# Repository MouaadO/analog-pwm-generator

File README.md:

# Analog PWM Generator with Adjustable Dead Time

**20–100 kHz · Complementary 5 V outputs · Stackable control PCB**

An analog PWM generator with adjustable frequency, duty cycle and dead time. The circuit uses a shared triangular carrier, comparison thresholds and output buffers. Its stackable PCB supplies the switching commands for the [58 W synchronous buck converter](https://github.com/MouaadO/synchronous-buck-converter), the second project in the electric-scooter auxiliary-power system.

**Project team:** Amani Mouaad and Cheiffou Melissa.  
**IFP SCHOOL · Powertrain · 2026/2027**

## The control half of a two-board system

The PWM board handles the low-level timing commands. The buck power board receives those commands through the Uno Rev3-compatible headers and drives its two power MOSFETs. Keeping the boards separate makes the timing circuit easy to adjust and the power stage easy to inspect.

| Function | Design target |
|---|---|
| Outputs | Two complementary PWM signals |
| Switching frequency | 20–100 kHz |
| Duty command | 0–100%, selected from a potentiometer or external SMA input |
| Dead-time adjustment | Up to 10% of the switching period |
| Logic levels | Nominal 0 V / 5 V |
| Drive current | More than 20 mA source and sink per output |
| Supply | 7–10 V DC, centre-positive barrel jack |

## How the signal becomes PWM

1. **Carrier generation:** An integrator produces a rising/falling triangular voltage. A comparator with hysteresis reverses the clock at the carrier limits.
2. **Command selection:** The selector chooses the duty potentiometer or the external SMA command.
3. **Threshold generation:** A resistor network combines the command with the dead-time setting to establish two comparison levels.
4. **Comparison:** The triangle crosses those levels at different instants, creating the two complementary pulse allocations and their non-overlap intervals.
5. **Output drive:** The buffer stages drive OUT1 and OUT2. Endpoint detectors establish constant states for external commands outside the operating interval.

## Oscillator and timing equations

For timing resistance $R_t$ and integrator capacitor $C_{INT}$:

$$I=\frac{CLOCK-V_m}{R_t},\qquad
\frac{dV_{TRI}}{dt}=-\frac{I}{C_{INT}}$$

The comparator limits and the integrator slope determine the period. For the chosen resistor ratio, the nominal frequency relation is:

$$f\simeq\frac{3}{R_tC_{INT}}$$

The shared carrier keeps the frequency, command and dead-time comparison tied to one switching period. Detailed threshold and frequency calculations are in the [design notes](docs/design-notes.md).

## Current stackable PCB

The current board is **75 × 53 mm**, with a 7 mm extension on the potentiometer side. The extension places the outward-facing controls, regulator and input connectors in the exposed area of the two-board assembly. The 32 mating contacts retain the official Uno Rev3 pattern.

### Top 3D view

### Header connections to the buck board

| Signal | PWM-board pad | Uno contact |
|---|---|---|
| OUT1 / PWM1 | J4 pin 9 | D9 |
| OUT2 / PWM2 | J4 pin 8 | D10 |
| Common ground | J4 pin 4; J6 pins 6–7 | GND |

The upper board is the [synchronous buck converter](https://github.com/MouaadO/synchronous-buck-converter). Its battery input and 12 V gate-driver supply use separate power terminals.

### Front and back layers

| Front copper | Back copper |
|---|---|
|  |  |

Signal tracks use 0.25 mm widths, PWM output routes 0.40 mm, and supply/ground routes 0.50 mm. The front copper fill distributes 5 V; the back fill provides ground. Local footprints and bundled models define the potentiometers, connectors and IC packages.

### Complete schematic

## Recorded LTspice results

The existing simulation uses the 7805 supply model. The PCB assembly uses the selected LF50ABV regulator. The following values are the recorded **LTspice results** for the supplied simulation settings:

| Quantity | Result |
|---|---:|
| Frequency endpoints | 19.99 kHz / 99.69 kHz |
| Output LOW / HIGH | 0.082 V / 4.916 V |
| Source/sink current | Approximately 26.86 mA per output |
| Fast-setting non-overlap gaps | 0.980 µs / 0.984 µs |

## Open and run

For the hardware, open [pcb/Analog_PWM.kicad_pro](pcb/Analog_PWM.kicad_pro) in KiCad 8 or newer. In PCB Editor, press **Alt+3** for the 3D viewer. Keep the local symbol library, footprint library, tables and `3dmodels` folder beside the project.

For simulation, open `simulation/analog_pwm_dead_time.asc` in LTspice and run its transient analysis. Probe `TRI`, `CMD`, `LOW`, `HIGH`, `OUT1` and `OUT2`. Parameters `FP`, `DP`, `DTP`, `SOURCE` and `VD` select the operating settings.

## Files and tools

| Location | Contents |
|---|---|
| `pcb/` | KiCad schematic, board, local libraries, assembly BOM and purchasing workbook |
| `pcb/Manufacturing/` | Gerbers and plated/non-plated drill outputs |
| `simulation/` | LTspice schematic, symbols and component libraries |
| [Design notes](docs/design-notes.md) | Oscillator, duty and threshold calculations |
| `docs/images/` | PCB, schematic and stacked-system renders |
| `docs/datasheets/` | Component datasheets |

**Tools:** LTspice, KiCad, manufacturer package drawings and local 3D models.

## Related projects

[58 W Synchronous Buck Converter](https://github.com/MouaadO/synchronous-buck-converter) · [Inverter Modulation and PWM](https://github.com/MouaadO/inverter-pwm-experimental-validation)

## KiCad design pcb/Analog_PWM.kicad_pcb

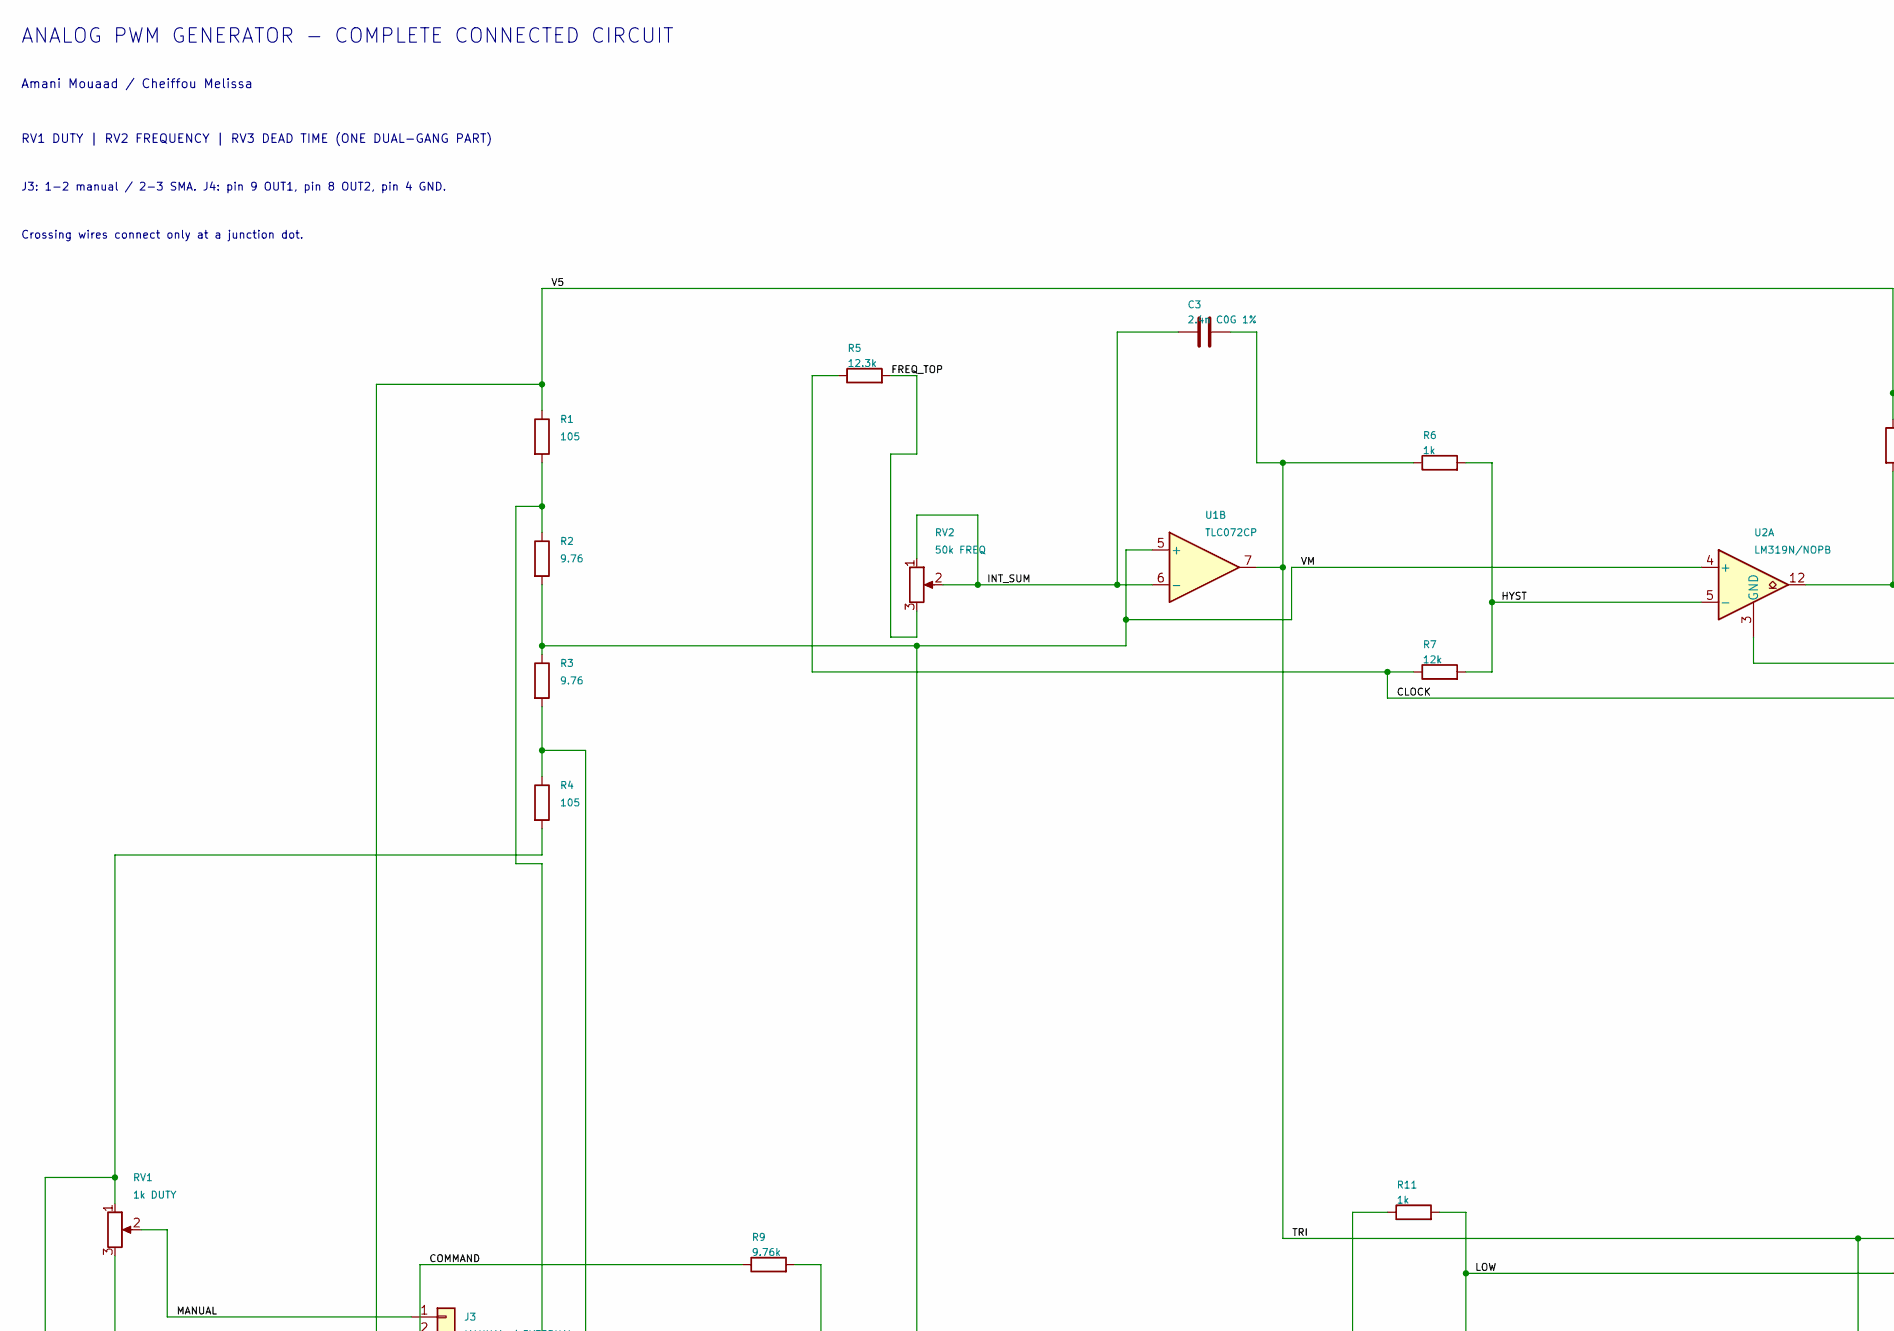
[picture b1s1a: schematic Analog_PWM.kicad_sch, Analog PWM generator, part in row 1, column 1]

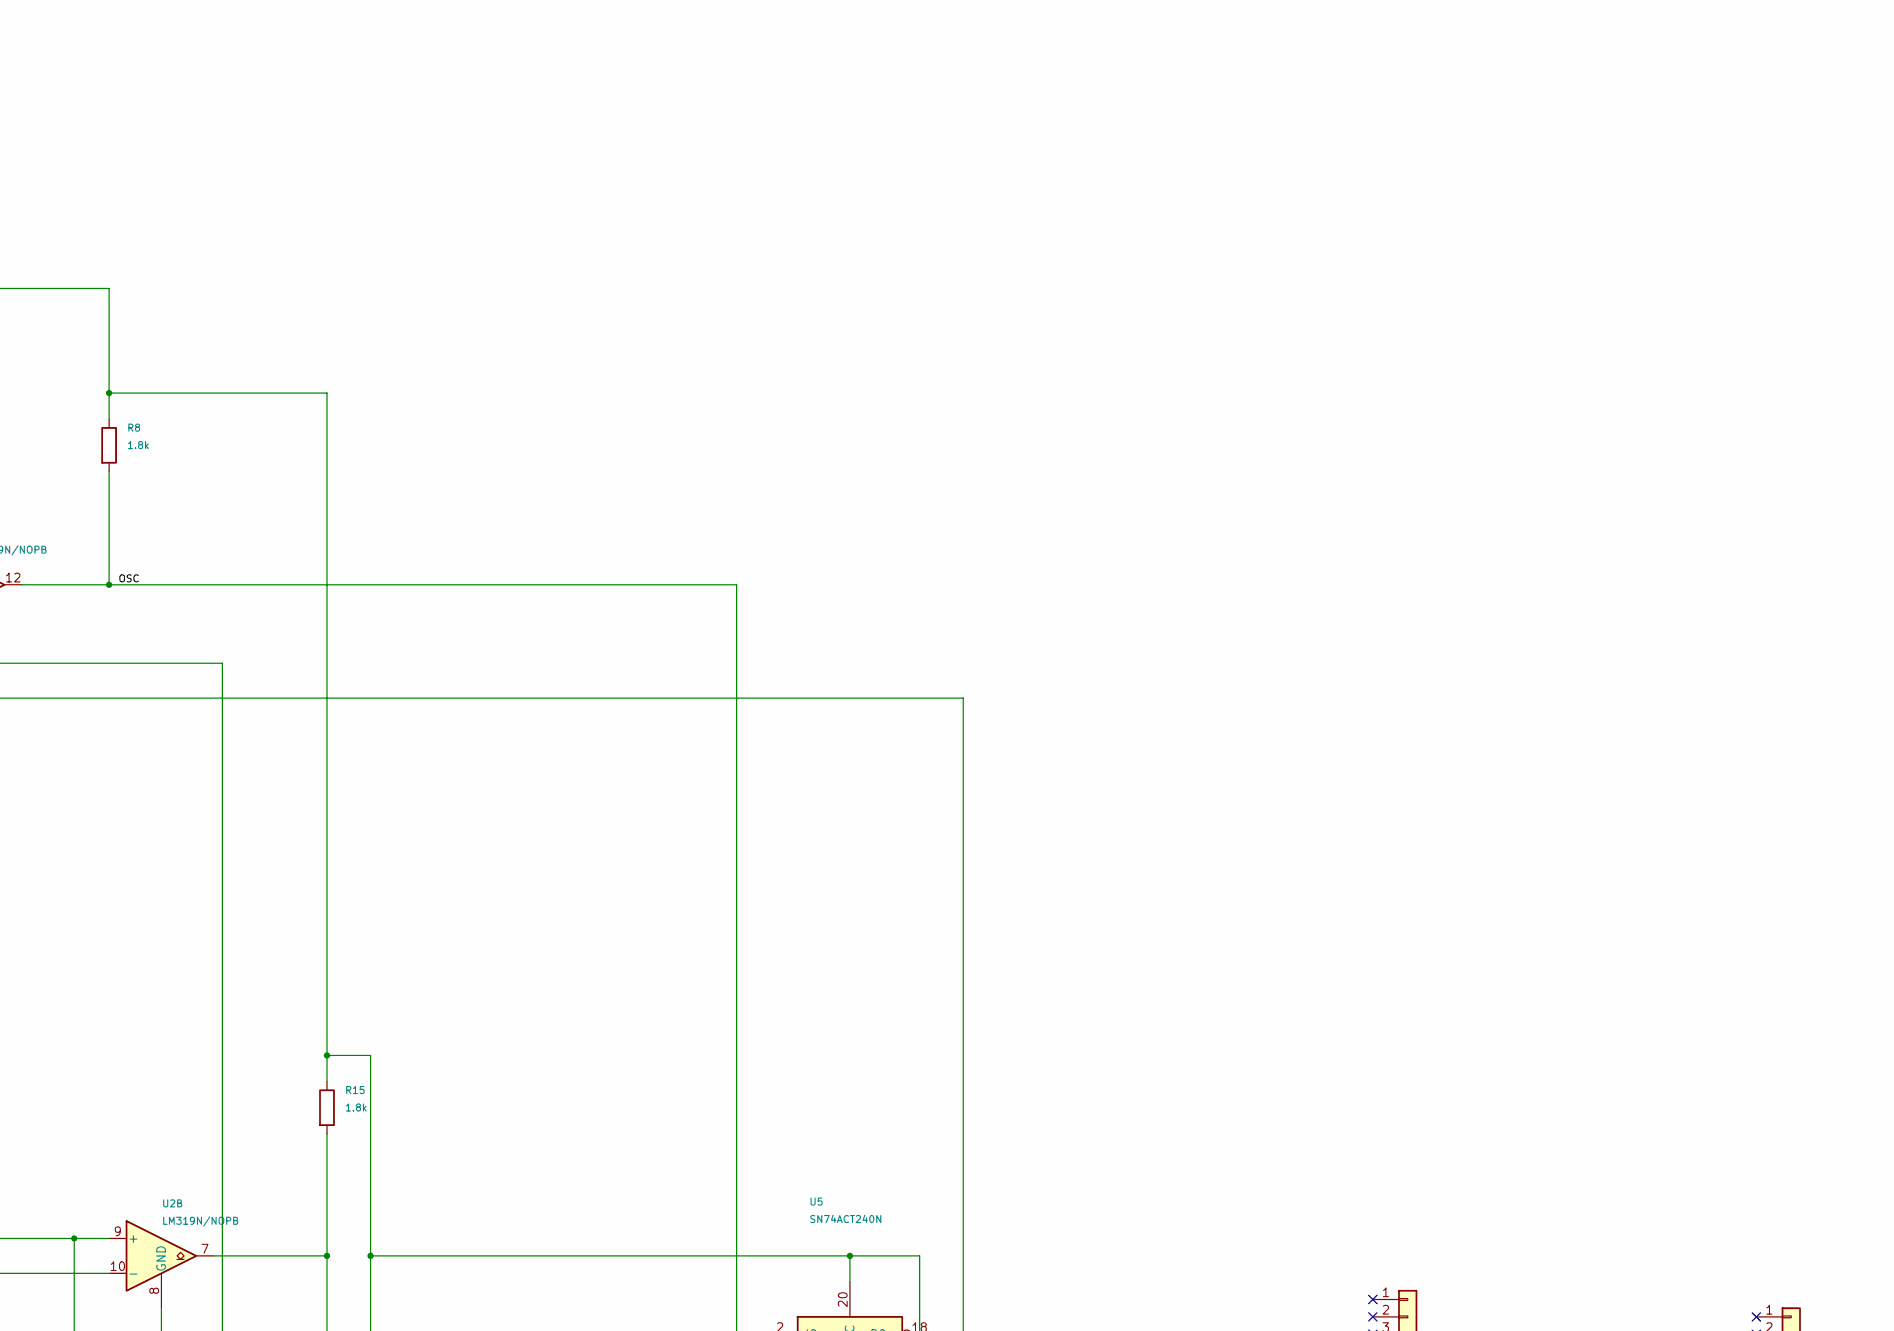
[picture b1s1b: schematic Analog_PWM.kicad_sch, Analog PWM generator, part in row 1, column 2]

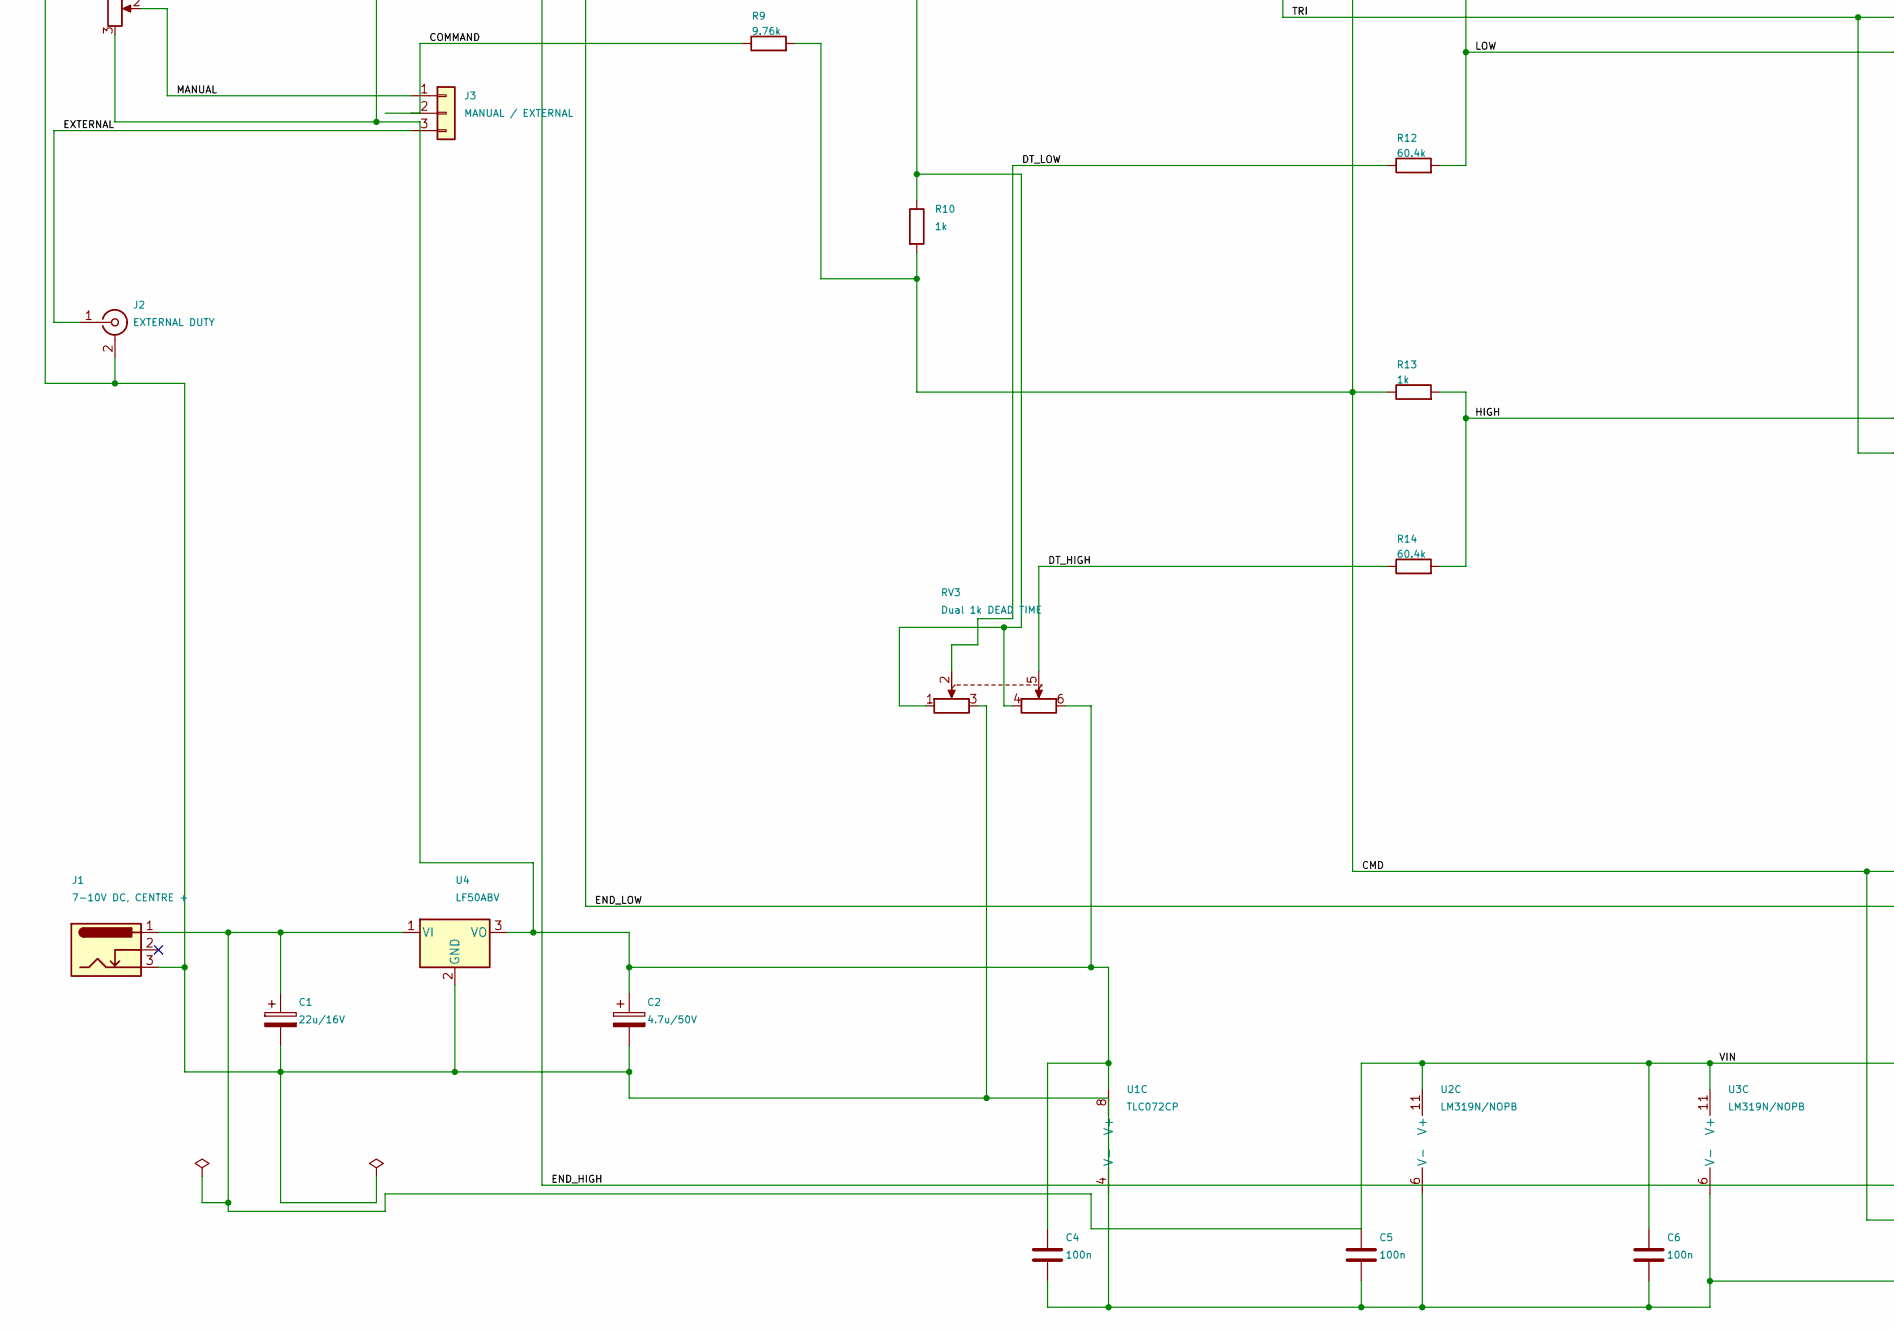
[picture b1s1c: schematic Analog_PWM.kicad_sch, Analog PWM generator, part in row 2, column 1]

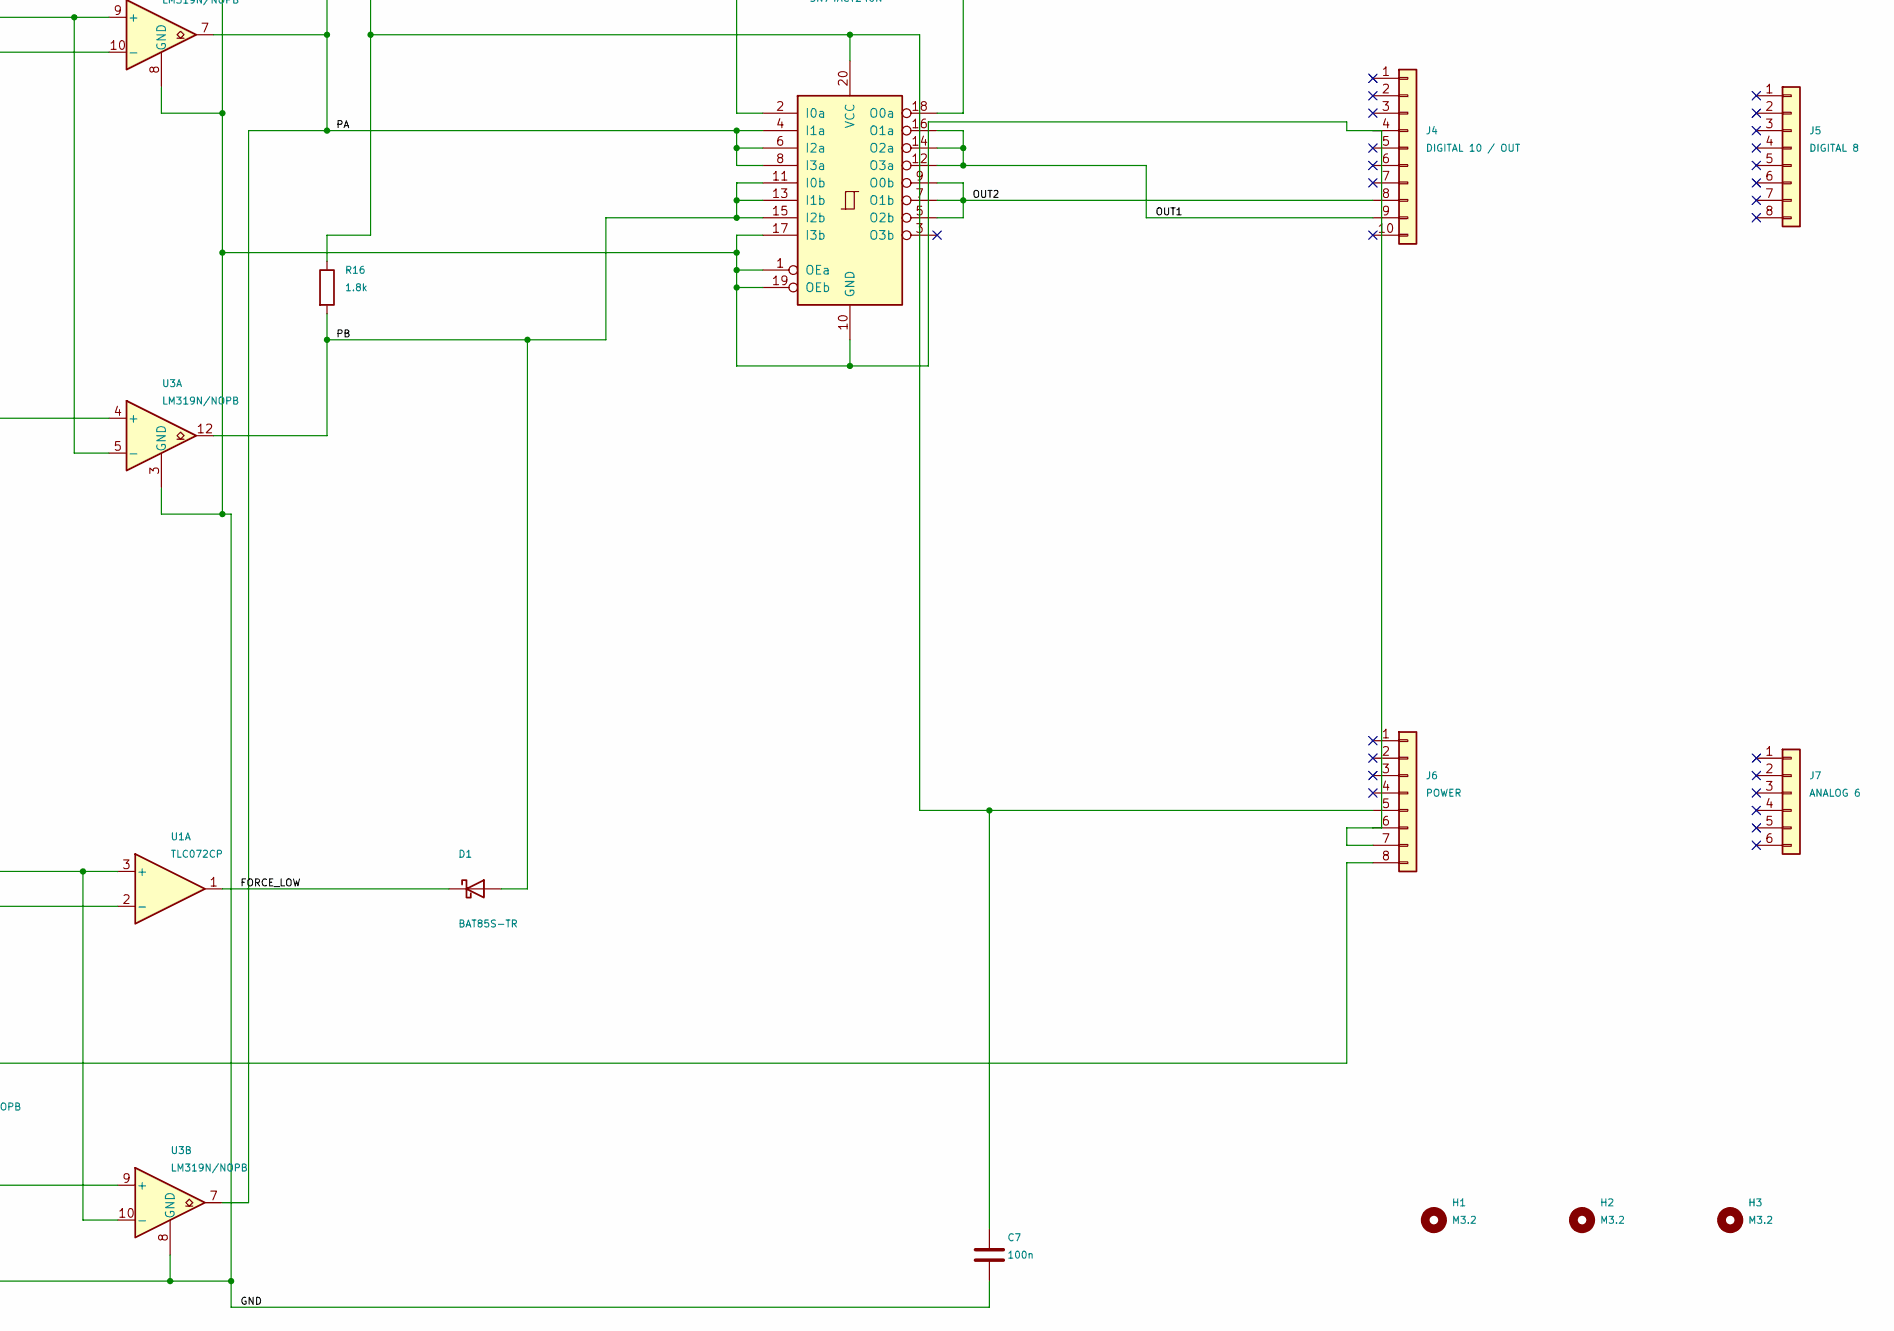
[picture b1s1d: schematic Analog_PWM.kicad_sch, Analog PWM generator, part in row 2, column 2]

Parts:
C1: 22u/16V; CP_Radial_D5.0mm_P2.00mm; MPN MCGPR16V226M5X11
C2: 4.7u/50V; CP_Radial_D5.0mm_P2.50mm; MPN EEU-FC1H4R7H
C3: 2.4n C0G 1%; C317_5.08mm; MPN C317C242F3G5TA
C4, C5, C6, C7: 100n; Vishay_K15_P2.5mm; MPN K104K15X7RF5TL2
D1: BAT85S-TR; D_DO-35_SOD27_P7.62mm_Horizontal; MPN BAT85S-TR
H1, H2, H3: M3.2; MountingHole_3.2mm
J1: 7-10V DC, CENTRE +; BarrelJack_CUI_PJ-102AH_Horizontal; MPN PJ-102AH
J2: EXTERNAL DUTY; Mueller_BU1420701236; MPN BU-1420701236
J3: MANUAL / EXTERNAL; PinSocket_1x03_P2.54mm_Vertical; MPN PPTC031LFBN-RC
J4: DIGITAL 10 / OUT; PinSocket_1x10_P2.54mm_Vertical; MPN PPTC101LFBN-RC
J5: DIGITAL 8; PinSocket_1x08_P2.54mm_Vertical; MPN PPTC081LFBN-RC
J6: POWER; PinSocket_1x08_P2.54mm_Vertical; MPN PPTC081LFBN-RC
J7: ANALOG 6; PinSocket_1x06_P2.54mm_Vertical; MPN PPTC061LFBN-RC
R1, R4: 105; R_Axial_DIN0207_L6.3mm_D2.5mm_P7.62mm_Horizontal; MPN MFR-25FBF52-105R
R2, R3: 9.76; R_Axial_DIN0204_L3.6mm_D1.6mm_P5.08mm_Horizontal; MPN MBA02040C9768FC100
R5: 12.3k; R_Axial_DIN0207_L6.3mm_D2.5mm_P7.62mm_Horizontal; MPN RNF14BTC12K3
R6, R10, R11, R13: 1k; R_Axial_DIN0207_L6.3mm_D2.5mm_P7.62mm_Horizontal; MPN MFR-25FBF52-1K
R7: 12k; R_Axial_DIN0207_L6.3mm_D2.5mm_P7.62mm_Horizontal; MPN MFR-25FBF52-12K
R8, R15, R16: 1.8k; R_Axial_DIN0207_L6.3mm_D2.5mm_P7.62mm_Horizontal; MPN MFR-25FBF52-1K8
R9: 9.76k; R_Axial_DIN0207_L6.3mm_D2.5mm_P7.62mm_Horizontal; MPN MFR-25FBF52-9K76
R12, R14: 60.4k; R_Axial_DIN0207_L6.3mm_D2.5mm_P7.62mm_Horizontal; MPN MFR-25FRF52-60K4
RV1: 1k DUTY; Bourns_PTV09A2_20mm; MPN PTV09A-2020F-B102
RV2: 50k FREQ; Bourns_PTV09A2; MPN PTV09A-2015F-B503
RV3: Dual 1k DEAD TIME; SameSky_PTN16_A_Dual; MPN PTN16-A01220K1B2
U1: TLC072CP; DIP-8_W7.62mm; MPN TLC072CP
U2, U3: LM319N/NOPB; DIP-14_W7.62mm; MPN LM319N/NOPB
U4: LF50ABV; TO-220-3_Vertical; MPN LF50ABV
U5: SN74ACT240N; DIP-20_W7.62mm; MPN SN74ACT240N

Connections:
/CLOCK: R5.1, R7.1, U5.18 (O0a)
/CMD: R9.2, R10.2, R11.1, R13.1, U1.3 (+), U3.10 (-)
/COMMAND: J3.2, R9.1
/DT_HIGH: R14.1, RV3.5
/DT_LOW: R12.1, RV3.2
/END_HIGH: R1.2, R2.1, U3.9 (+)
/END_LOW: R3.2, R4.1, U1.2 (-)
/EXTERNAL: J2.1 (In), J3.3
/FORCE_LOW: D1.1 (K), U1.1
/FREQ_TOP: R5.2, RV2.3
/GND: C1.2, C2.2, C4.2, C5.2, C6.2, C7.2, J1.3, J2.2 (Ext), J4.4, J6.6, J6.7, R4.2, RV1.1, RV3.3, U1.4 (V-), U2.3 (GND), U2.6 (V-), U2.8 (GND), U3.3 (GND), U3.6 (V-), U3.8 (GND), U4.2 (GND), U5.1 (OEa), U5.10 (GND), U5.17 (I3b), U5.19 (OEb)
/HIGH: R13.2, R14.2, U3.4 (+)
/HYST: R6.2, R7.2, U2.5 (-)
/INT_SUM: C3.1, RV2.1, RV2.2, U1.6 (-)
/LOW: R11.2, R12.2, U2.10 (-)
/MANUAL: J3.1, RV1.2
/OSC: R8.2, U2.12, U5.2 (I0a)
/OUT1: J4.9, U5.12 (O3a), U5.14 (O2a), U5.16 (O1a)
/OUT2: J4.8, U5.5 (O2b), U5.7 (O1b), U5.9 (O0b)
/PA: R15.2, U2.7, U3.7, U5.4 (I1a), U5.6 (I2a), U5.8 (I3a)
/PB: D1.2 (A), R16.2, U3.12, U5.11 (I0b), U5.13 (I1b), U5.15 (I2b)
/TRI: C3.2, R6.1, U1.7, U2.9 (+), U3.5 (-)
/V5: C2.1, C4.1, C7.1, J6.5, R1.1, R8.1, R15.1, R16.1, RV1.3, RV3.6, U1.8 (V+), U4.3 (VO), U5.20 (VCC)
/VIN: C1.1, C5.1, C6.1, J1.1, J6.8, U2.11 (V+), U3.11 (V+), U4.1 (VI)
/VM: R2.2, R3.1, R10.1, RV3.1, RV3.4, U1.5 (+), U2.4 (+)

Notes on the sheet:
ANALOG PWM GENERATOR - COMPLETE CONNECTED CIRCUIT
Amani Mouaad / Cheiffou Melissa
RV1 DUTY | RV2 FREQUENCY | RV3 DEAD TIME (ONE DUAL-GANG PART)
J3: 1-2 manual / 2-3 SMA. J4: pin 9 OUT1, pin 8 OUT2, pin 4 GND.
Crossing wires connect only at a junction dot.

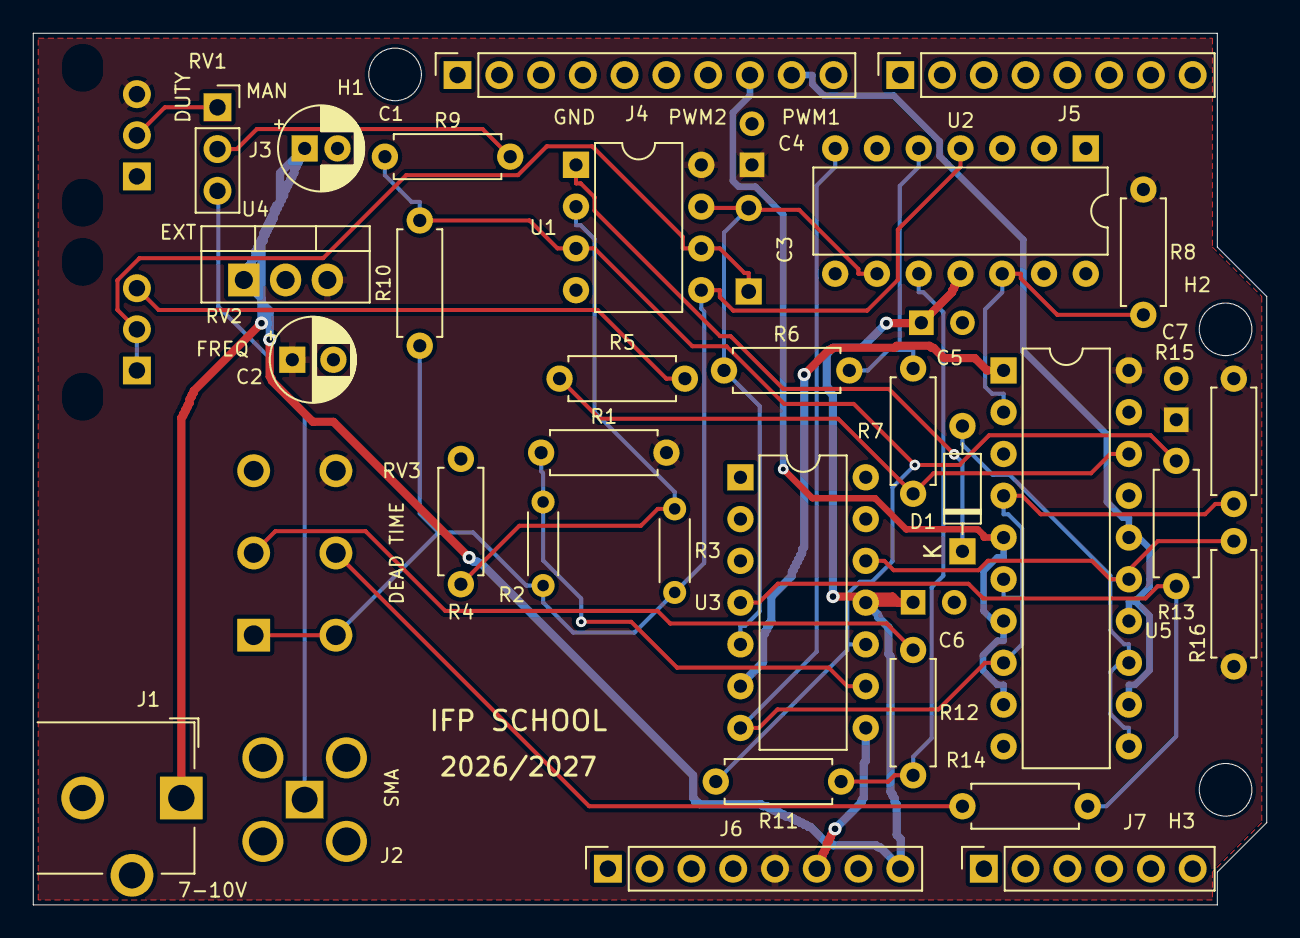
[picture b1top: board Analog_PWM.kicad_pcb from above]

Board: 2 copper layers, 75.0 x 53.0 mm, 42 parts (0 on the bottom side), 25 nets.
